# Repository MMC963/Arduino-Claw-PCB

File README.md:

# Arduino Claw PCB Redesign

## Overview

This project involved redesigning the electrical connections for an Arduino-controlled claw developed as part of a team-based engineering project. After identifying unreliable wire connections during testing, I independently developed a PCB redesign in KiCad to improve connection stability and reduce wiring issues.

## Problem Statement

During testing, loose wire connections caused inconsistent system performance. The existing wiring arrangement was unreliable, making it difficult to ensure consistent operation of the claw's electronic components.

## Design Approach

* **PCB Design:** Used KiCad to develop a PCB redesign aimed at improving wiring organization and connection reliability.
* **Hardware Integration:** Considered the electrical connections between the Arduino and the claw's electronic components.
* **Reliability:** Focused on reducing loose connections and improving the overall organization of the circuit.

## Tools Used

* KiCad
* Arduino
* Embedded C/C++

## Engineering Challenges

The primary challenge was identifying hardware connectivity as a potential source of system unreliability and developing a more structured electrical connection solution. The redesign focused on addressing the wiring issues observed during system testing.

## Project Outcome

Developed a PCB redesign concept to address wiring instability in the Arduino-controlled claw. This project strengthened my understanding of PCB design, hardware integration, and the importance of reliable electrical connections in embedded systems.

## Future Improvements

* Manufacture the PCB and validate the physical design.
* Test connection reliability under repeated claw operation.
* Refine the layout based on assembly and testing results.

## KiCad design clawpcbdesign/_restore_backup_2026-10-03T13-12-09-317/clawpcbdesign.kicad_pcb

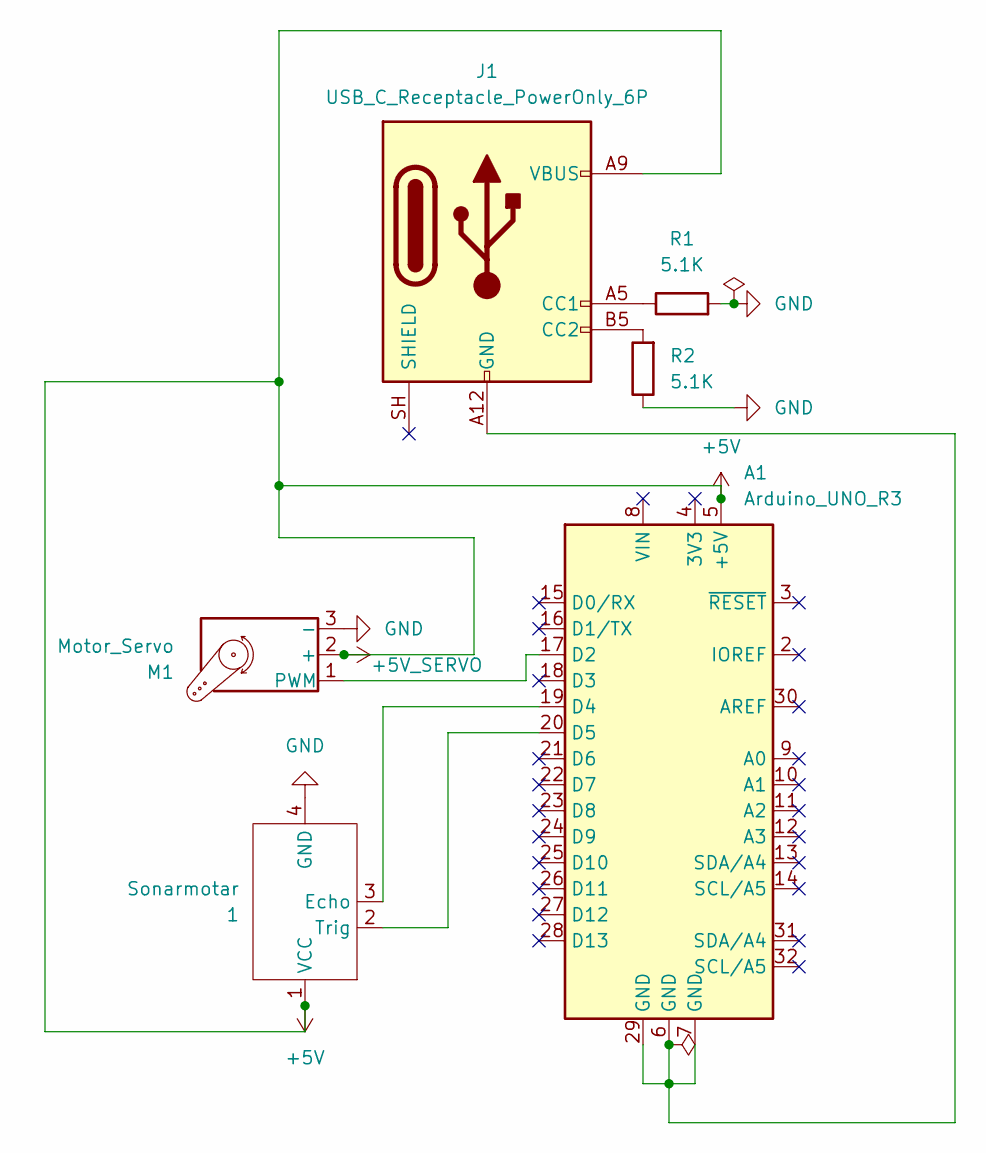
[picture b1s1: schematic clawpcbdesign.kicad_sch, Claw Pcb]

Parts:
1: Sonarmotar; Untitled
A1: Arduino_UNO_R3
J1: USB_C_Receptacle_PowerOnly_6P; USB_C_Receptacle_Amphenol_124019772112A
M1: Motor_Servo; PinHeader_1x03_P2.54mm_Vertical
R1, R2: 5.1K; R_Axial_DIN0516_L15.5mm_D5.0mm_P7.62mm_Vertical

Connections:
+5V: 1.1 (VCC), A1.5 (+5V), J1.A9 (VBUS), J1.B9 (VBUS), M1.2 (+)
GND: 1.4 (GND), M1.3 (-), R1.2, R2.1
unnamed: 1.3 (Echo), A1.19 (D4)
unnamed: 1.2 (Trig), A1.20 (D5)
unnamed: A1.17 (D2), M1.1 (PWM)
unnamed: A1.6 (GND), A1.7 (GND), A1.29 (GND), J1.A12 (GND), J1.B12 (GND)
unnamed: J1.A5 (CC1), R1.1
unnamed: J1.B5 (CC2), R2.2

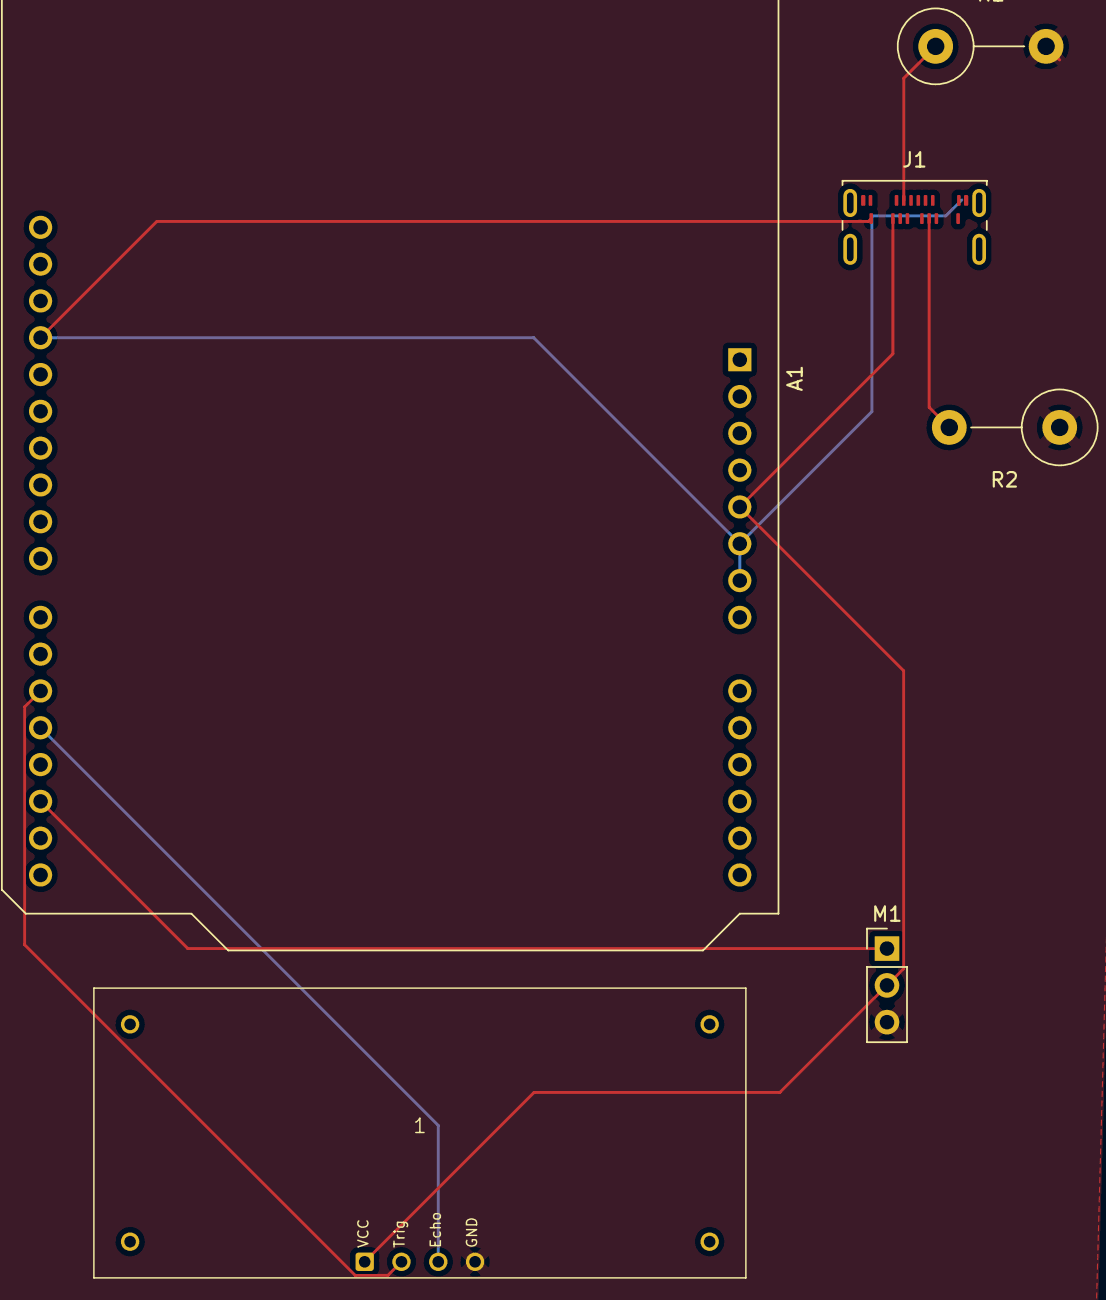
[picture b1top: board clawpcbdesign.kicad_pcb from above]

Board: 2 copper layers, 6 parts (0 on the bottom side), 8 nets.
